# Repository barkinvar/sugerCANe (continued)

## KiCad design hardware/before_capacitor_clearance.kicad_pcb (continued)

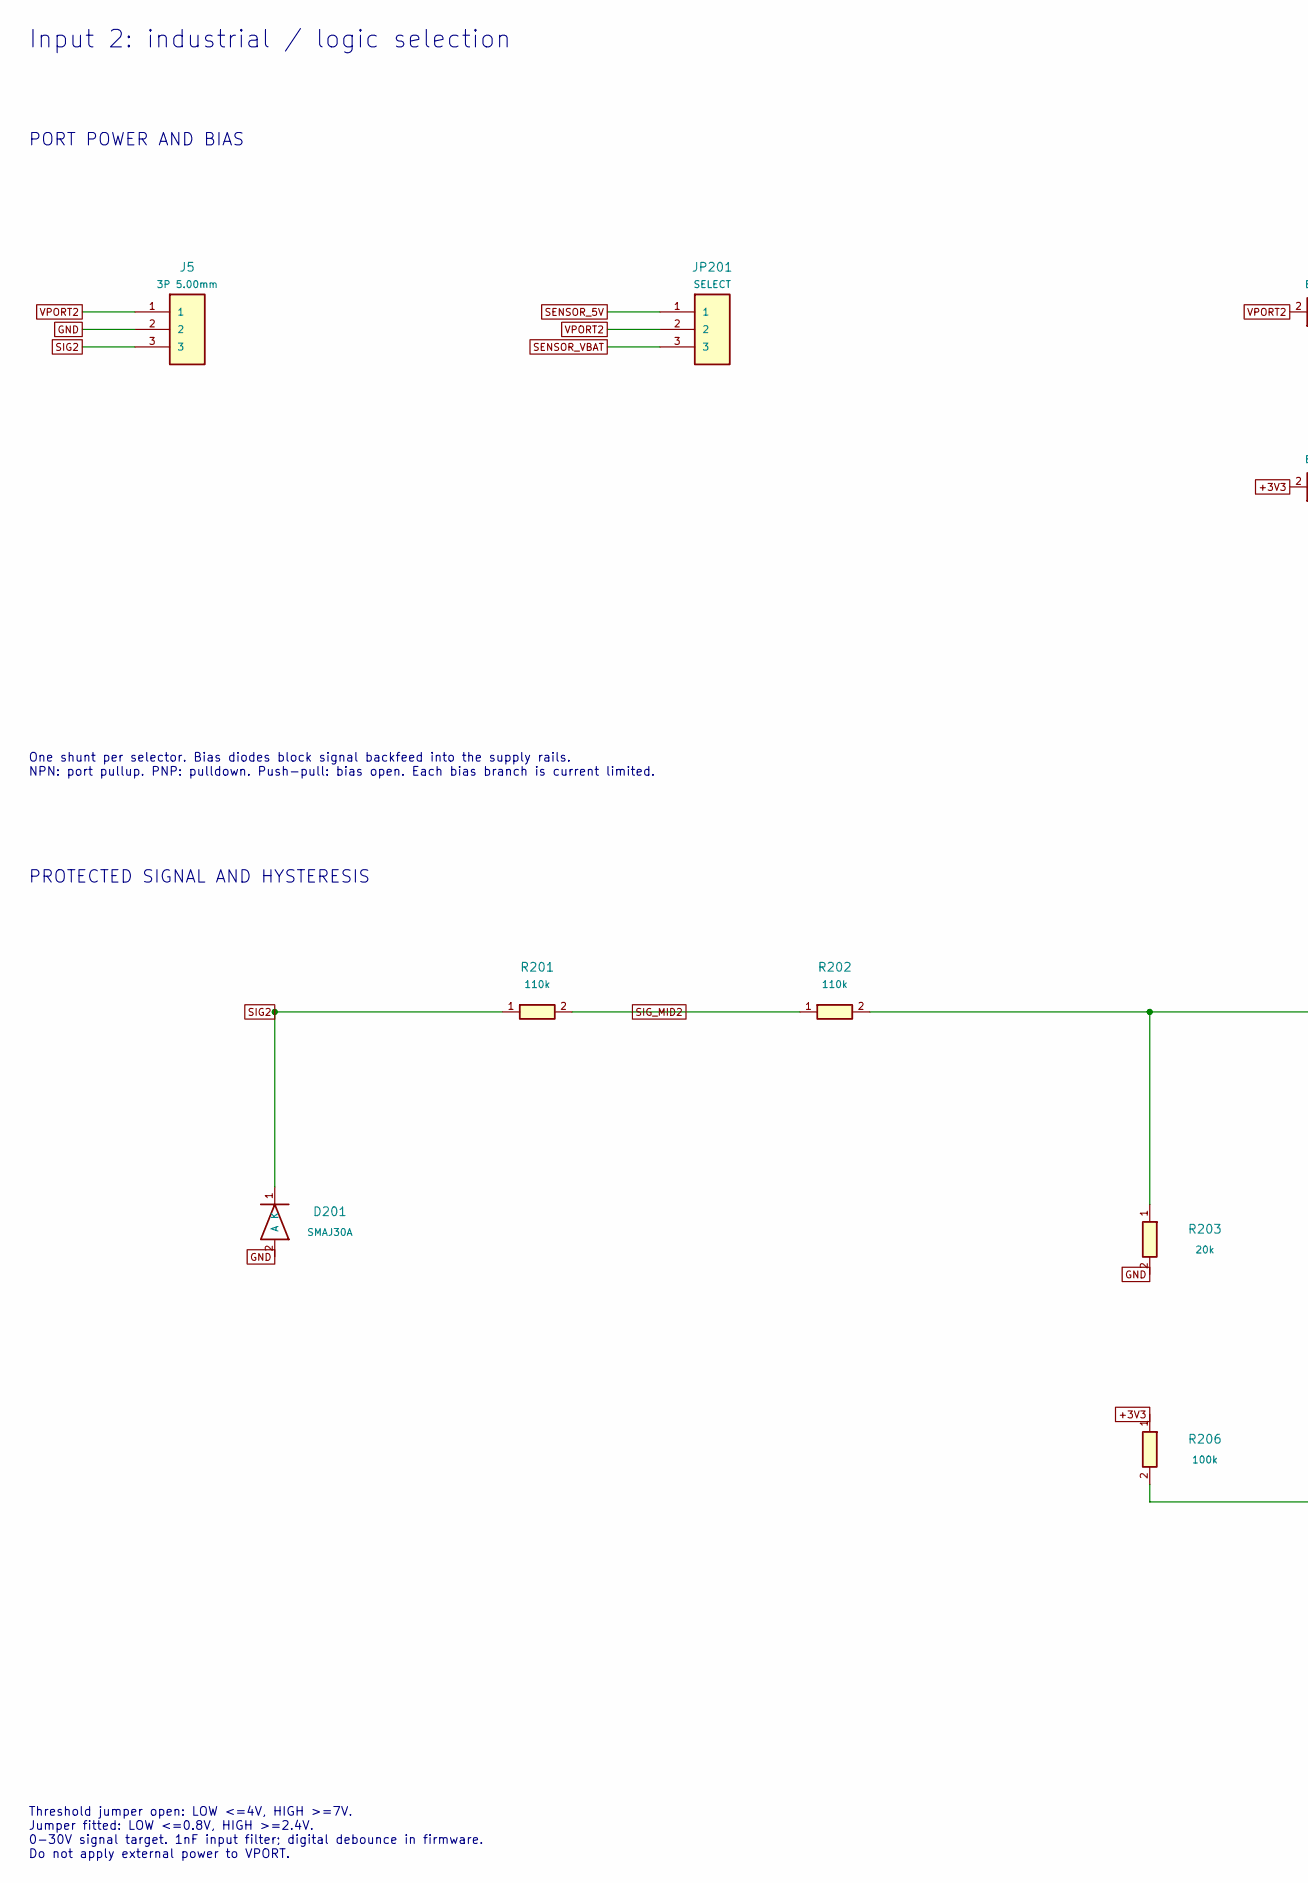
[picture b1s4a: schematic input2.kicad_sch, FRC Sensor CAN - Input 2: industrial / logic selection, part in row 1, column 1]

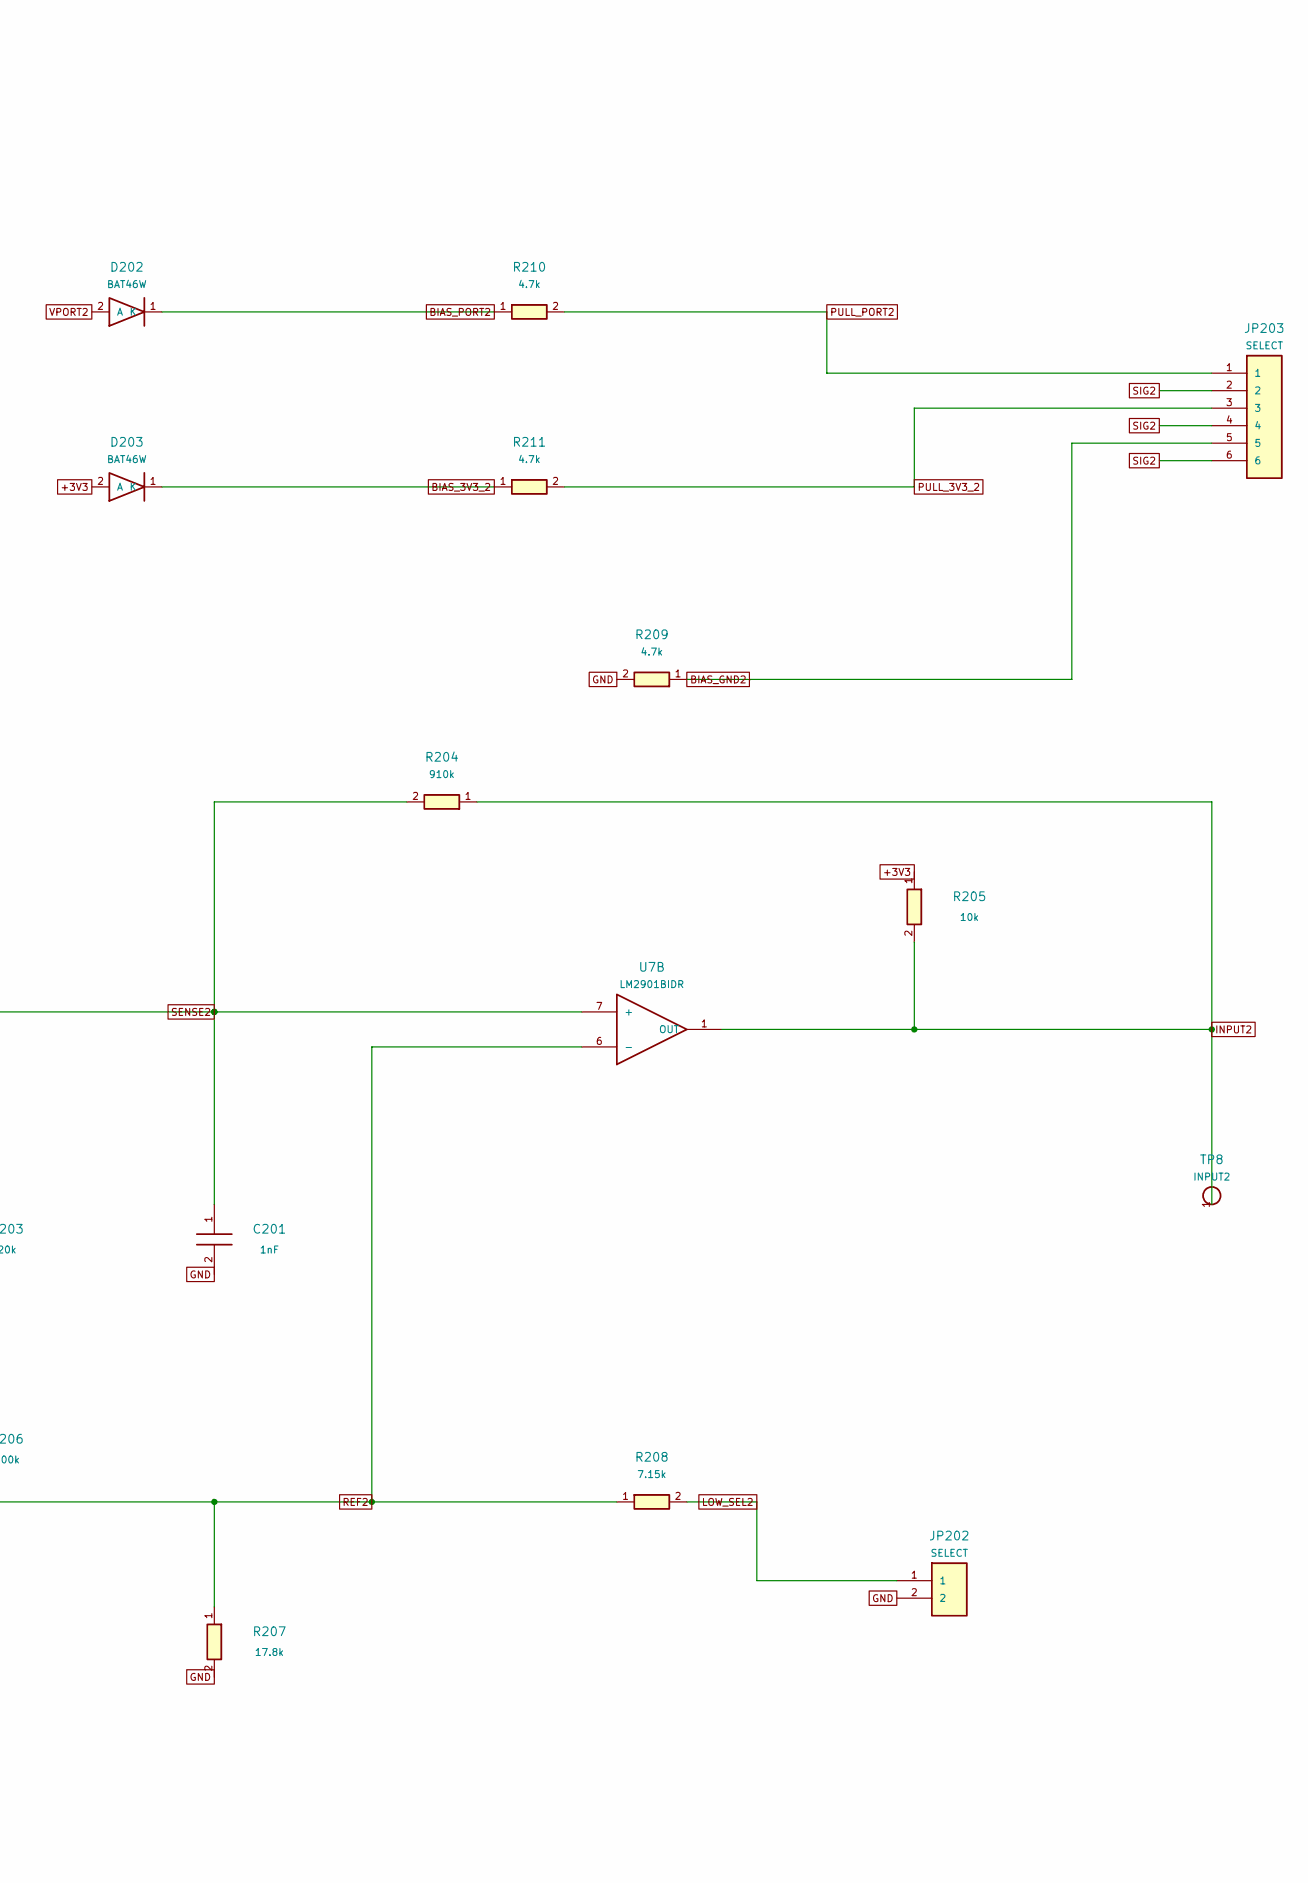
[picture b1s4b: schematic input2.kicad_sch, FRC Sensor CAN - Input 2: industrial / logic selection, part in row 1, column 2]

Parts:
C201: 1nF; C_0805_2012Metric; MPN CC0805JRNPO9BN102
D201: SMAJ30A; D_SMA; MPN SMAJ30A
D202, D203: BAT46W; D_SOD-123; MPN BAT46W-E3-18
J5: 3P 5.00mm; Wuerth_691137710003; MPN 691137710003
JP201: SELECT; PinHeader_1x03_P2.54mm_Vertical; MPN M20-9990345
JP202: SELECT; PinHeader_1x02_P2.54mm_Vertical; MPN M20-9990245
JP203: SELECT; PinHeader_2x03_P2.54mm_Vertical; MPN M20-9980345
R201, R202: 110k; R_0805_2012Metric; MPN RC0805FR-07110KL
R203: 20k; R_0805_2012Metric; MPN RC0805FR-0720KL
R204: 910k; R_0805_2012Metric; MPN RC0805FR-07910KL
R205: 10k; R_0805_2012Metric; MPN RC0805FR-0710KL
R206: 100k; R_0805_2012Metric; MPN RC0805FR-07100KL
R207: 17.8k; R_0805_2012Metric; MPN ERJ-6ENF1782V
R208: 7.15k; R_0805_2012Metric; MPN RC0805FR-077K15L
R209: 4.7k; R_2010_5025Metric; MPN RC2010FK-074K7L
R210, R211: 4.7k; R_0805_2012Metric; MPN RC0805FR-074K7L
TP8: INPUT2; TestPoint_Pad_D2.0mm
U7: LM2901BIDR; SOIC-14_3.9x8.7mm_P1.27mm; MPN LM2901BIDR

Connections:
+3V3: D203.2 (A), R205.1, R206.1; also elsewhere on the board
BIAS_3V3_2: D203.1 (K), R211.1
BIAS_GND2: JP203.5, R209.1
BIAS_PORT2: D202.1 (K), R210.1
GND: C201.2, D201.2 (A), J5.2, JP202.2, R203.2, R207.2, R209.2; also elsewhere on the board
INPUT2: R204.1, R205.2, TP8.1, U7.1 (OUT); also elsewhere on the board
LOW_SEL2: JP202.1, R208.2
PULL_3V3_2: JP203.3, R211.2
PULL_PORT2: JP203.1, R210.2
REF2: R206.2, R207.1, R208.1, U7.6 (-)
SENSE2: C201.1, R202.2, R203.1, R204.2, U7.7 (+)
SENSOR_5V: JP201.1; also elsewhere on the board
SENSOR_VBAT: JP201.3; also elsewhere on the board
SIG2: D201.1 (K), J5.3, JP203.2, JP203.4, JP203.6, R201.1
SIG_MID2: R201.2, R202.1
VPORT2: D202.2 (A), J5.1, JP201.2

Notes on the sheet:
Input 2: industrial / logic selection
PORT POWER AND BIAS
One shunt per selector. Bias diodes block signal backfeed into the supply rails. NPN: port pullup. PNP: pulldown. Push-pull: bias open. Each bias branch is current limited.
PROTECTED SIGNAL AND HYSTERESIS
Threshold jumper open: LOW <=4V, HIGH >=7V. Jumper fitted: LOW <=0.8V, HIGH >=2.4V. 0-30V signal target. 1nF input filter; digital debounce in firmware. Do not apply external power to VPORT.

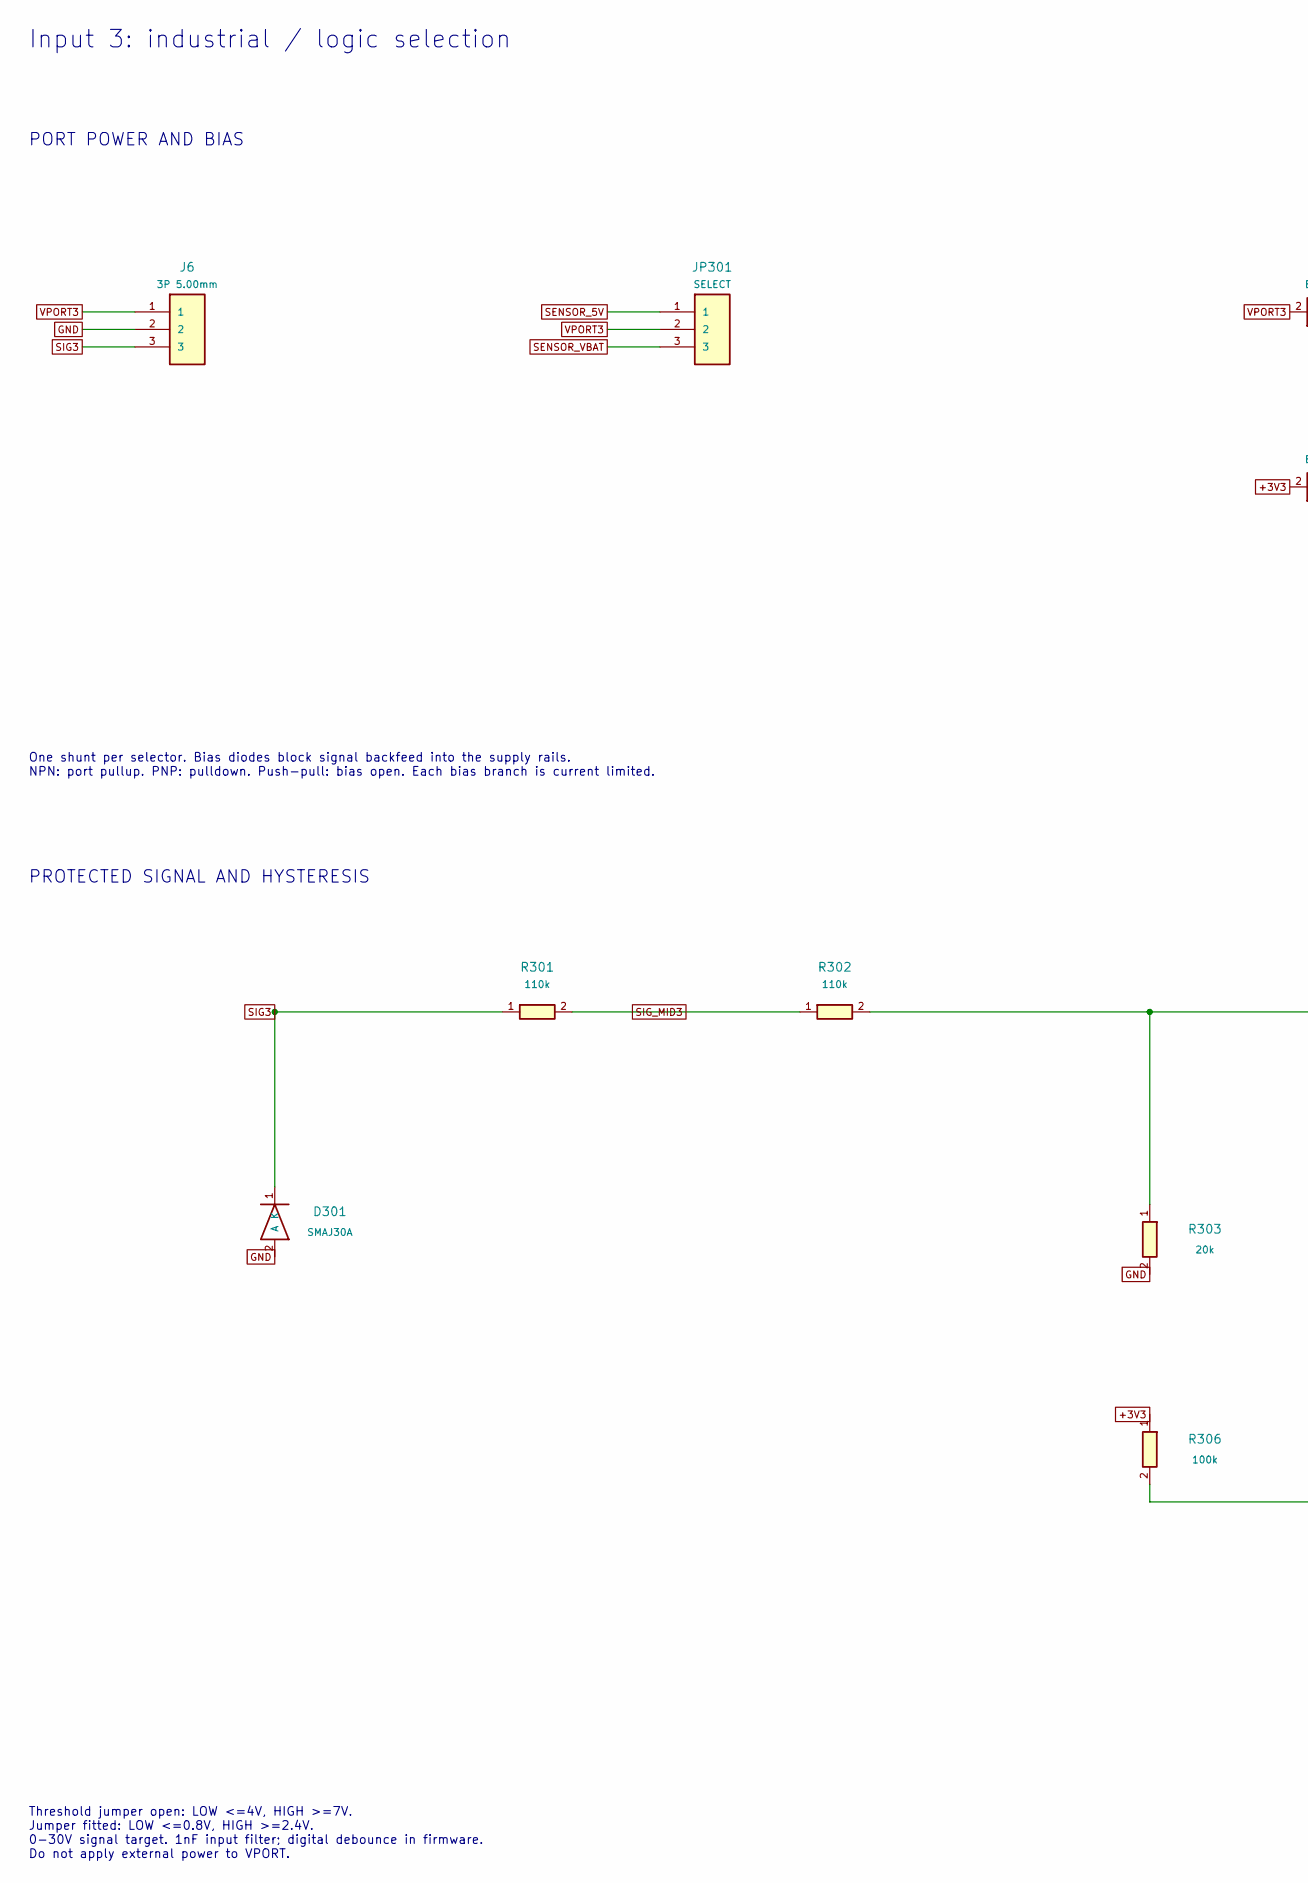
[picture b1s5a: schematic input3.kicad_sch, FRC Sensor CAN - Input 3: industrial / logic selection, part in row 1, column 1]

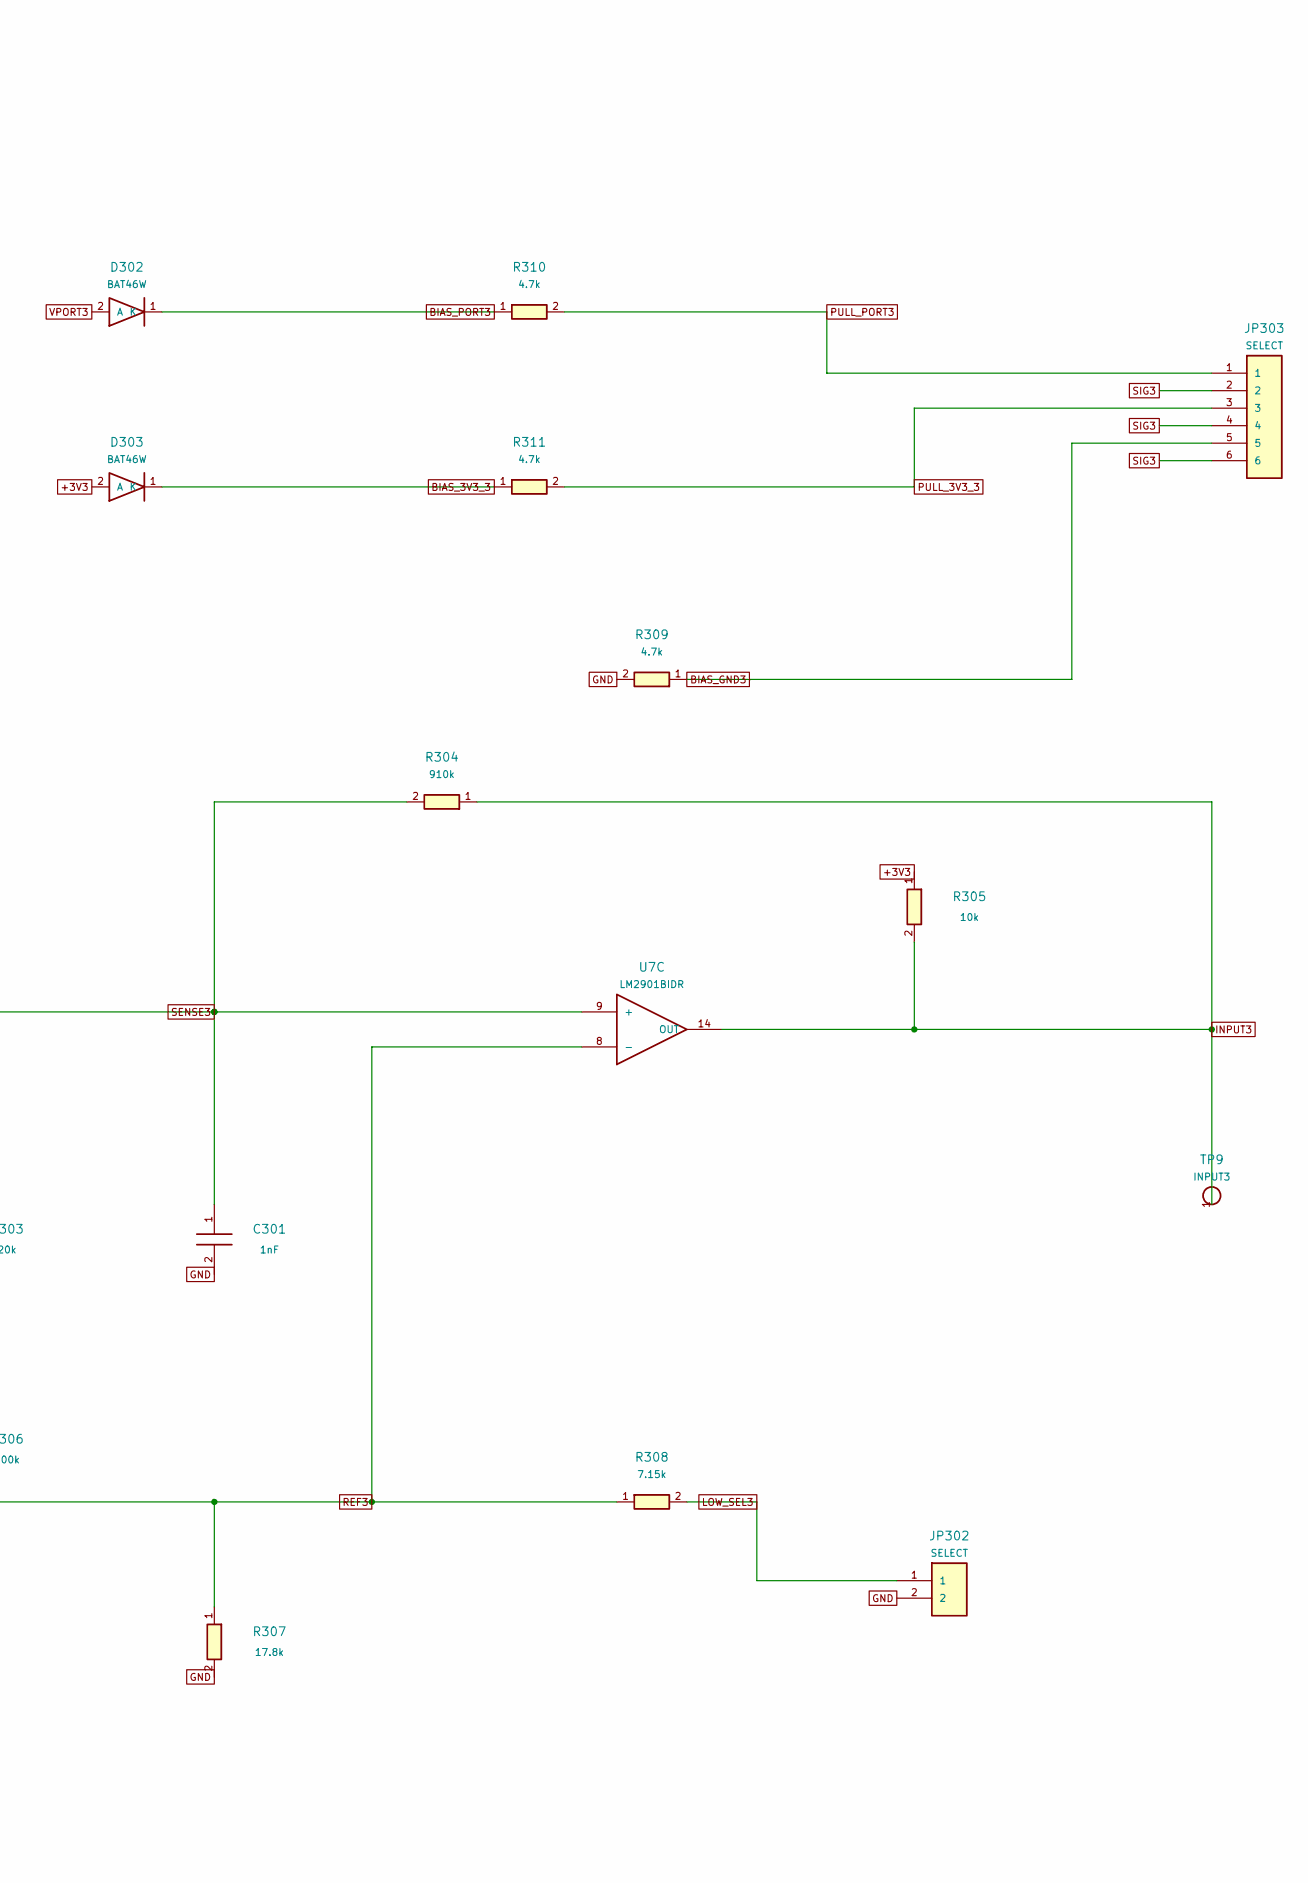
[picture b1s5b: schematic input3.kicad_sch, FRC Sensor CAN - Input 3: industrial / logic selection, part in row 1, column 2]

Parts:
C301: 1nF; C_0805_2012Metric; MPN CC0805JRNPO9BN102
D301: SMAJ30A; D_SMA; MPN SMAJ30A
D302, D303: BAT46W; D_SOD-123; MPN BAT46W-E3-18
J6: 3P 5.00mm; Wuerth_691137710003; MPN 691137710003
JP301: SELECT; PinHeader_1x03_P2.54mm_Vertical; MPN M20-9990345
JP302: SELECT; PinHeader_1x02_P2.54mm_Vertical; MPN M20-9990245
JP303: SELECT; PinHeader_2x03_P2.54mm_Vertical; MPN M20-9980345
R301, R302: 110k; R_0805_2012Metric; MPN RC0805FR-07110KL
R303: 20k; R_0805_2012Metric; MPN RC0805FR-0720KL
R304: 910k; R_0805_2012Metric; MPN RC0805FR-07910KL
R305: 10k; R_0805_2012Metric; MPN RC0805FR-0710KL
R306: 100k; R_0805_2012Metric; MPN RC0805FR-07100KL
R307: 17.8k; R_0805_2012Metric; MPN ERJ-6ENF1782V
R308: 7.15k; R_0805_2012Metric; MPN RC0805FR-077K15L
R309: 4.7k; R_2010_5025Metric; MPN RC2010FK-074K7L
R310, R311: 4.7k; R_0805_2012Metric; MPN RC0805FR-074K7L
TP9: INPUT3; TestPoint_Pad_D2.0mm
U7: LM2901BIDR; SOIC-14_3.9x8.7mm_P1.27mm; MPN LM2901BIDR

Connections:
+3V3: D303.2 (A), R305.1, R306.1; also elsewhere on the board
BIAS_3V3_3: D303.1 (K), R311.1
BIAS_GND3: JP303.5, R309.1
BIAS_PORT3: D302.1 (K), R310.1
GND: C301.2, D301.2 (A), J6.2, JP302.2, R303.2, R307.2, R309.2; also elsewhere on the board
INPUT3: R304.1, R305.2, TP9.1, U7.14 (OUT); also elsewhere on the board
LOW_SEL3: JP302.1, R308.2
PULL_3V3_3: JP303.3, R311.2
PULL_PORT3: JP303.1, R310.2
REF3: R306.2, R307.1, R308.1, U7.8 (-)
SENSE3: C301.1, R302.2, R303.1, R304.2, U7.9 (+)
SENSOR_5V: JP301.1; also elsewhere on the board
SENSOR_VBAT: JP301.3; also elsewhere on the board
SIG3: D301.1 (K), J6.3, JP303.2, JP303.4, JP303.6, R301.1
SIG_MID3: R301.2, R302.1
VPORT3: D302.2 (A), J6.1, JP301.2

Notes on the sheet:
Input 3: industrial / logic selection
PORT POWER AND BIAS
One shunt per selector. Bias diodes block signal backfeed into the supply rails. NPN: port pullup. PNP: pulldown. Push-pull: bias open. Each bias branch is current limited.
PROTECTED SIGNAL AND HYSTERESIS
Threshold jumper open: LOW <=4V, HIGH >=7V. Jumper fitted: LOW <=0.8V, HIGH >=2.4V. 0-30V signal target. 1nF input filter; digital debounce in firmware. Do not apply external power to VPORT.

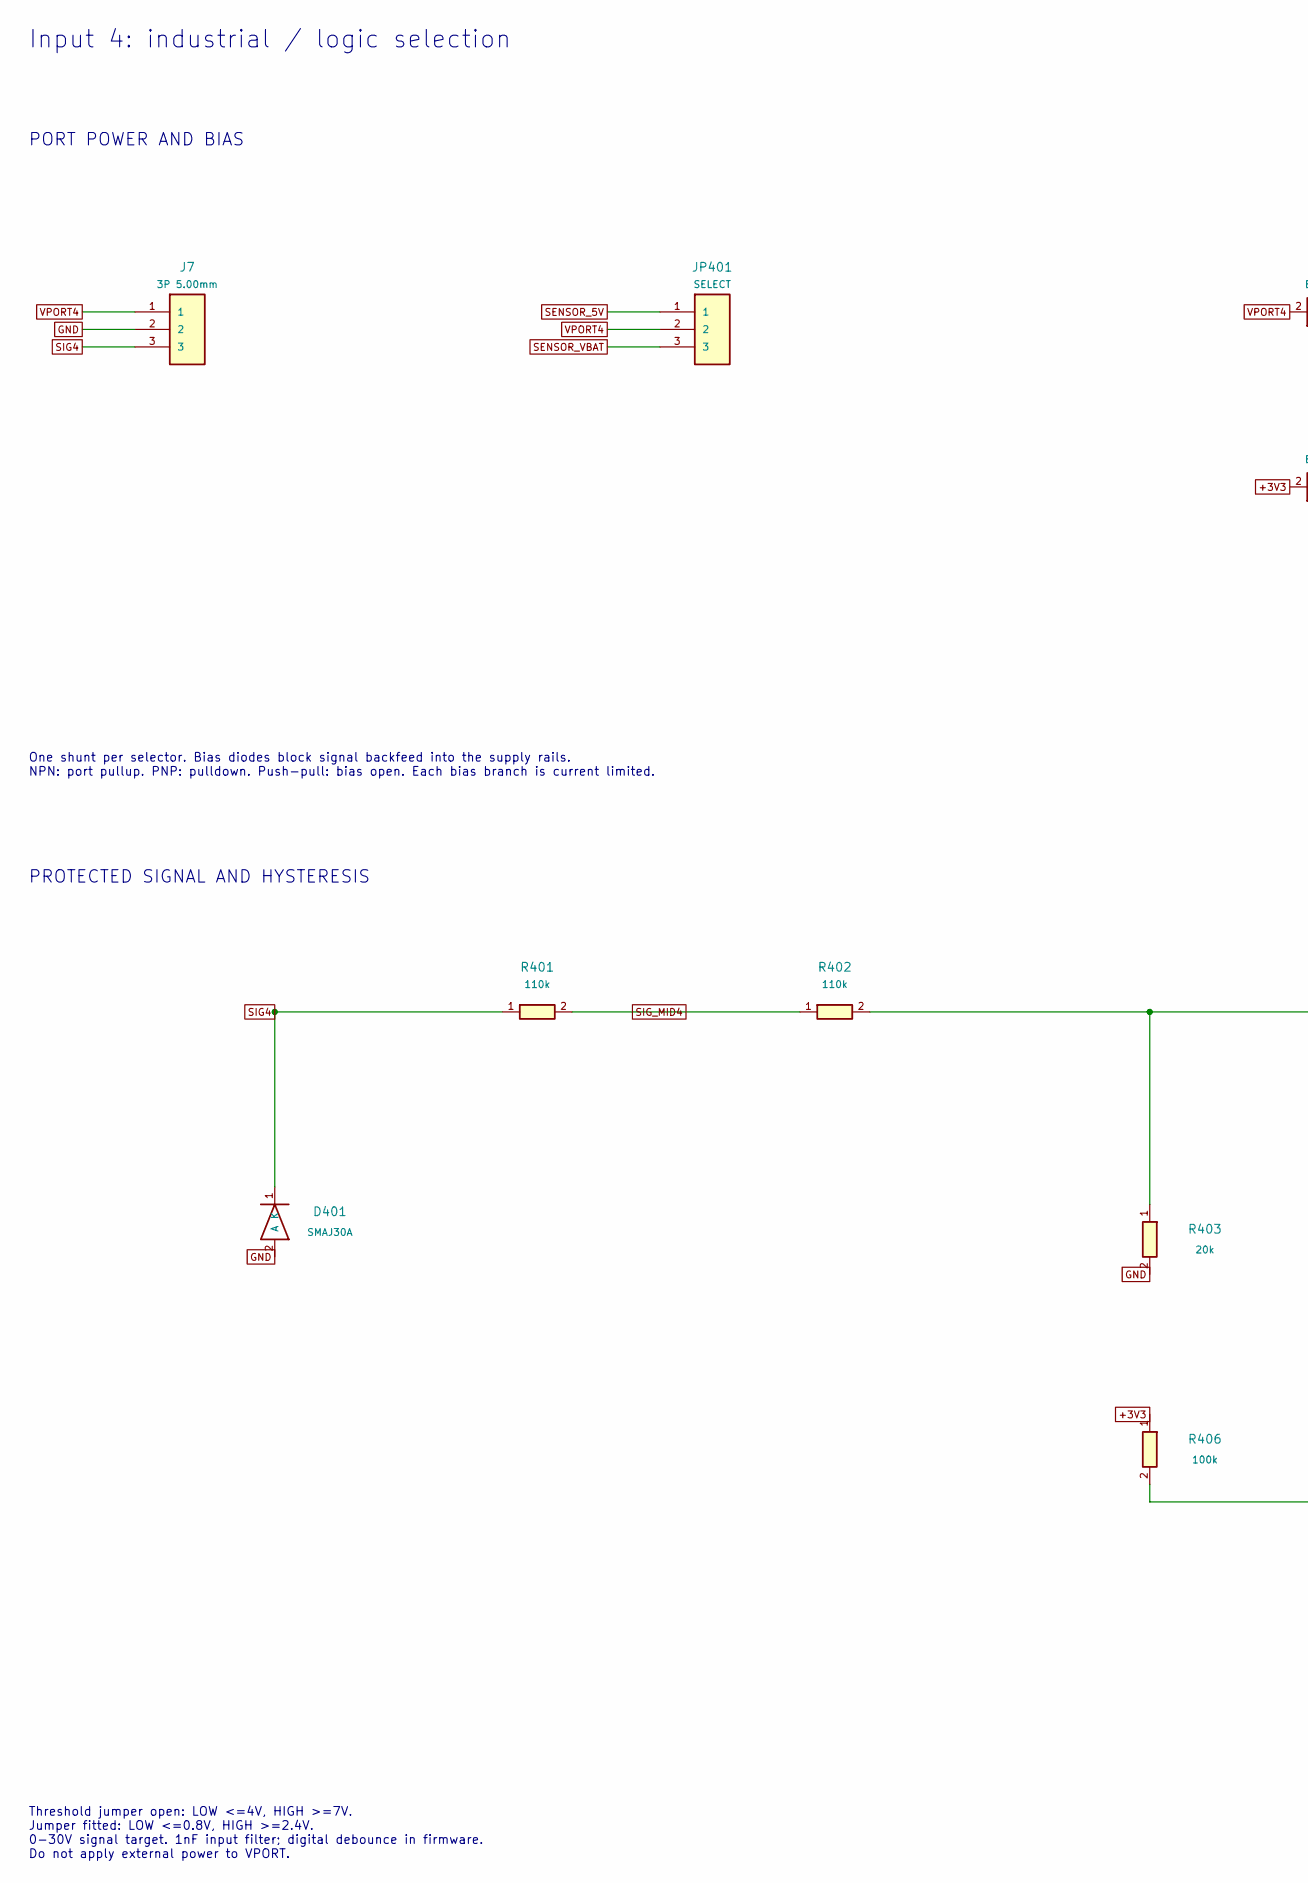
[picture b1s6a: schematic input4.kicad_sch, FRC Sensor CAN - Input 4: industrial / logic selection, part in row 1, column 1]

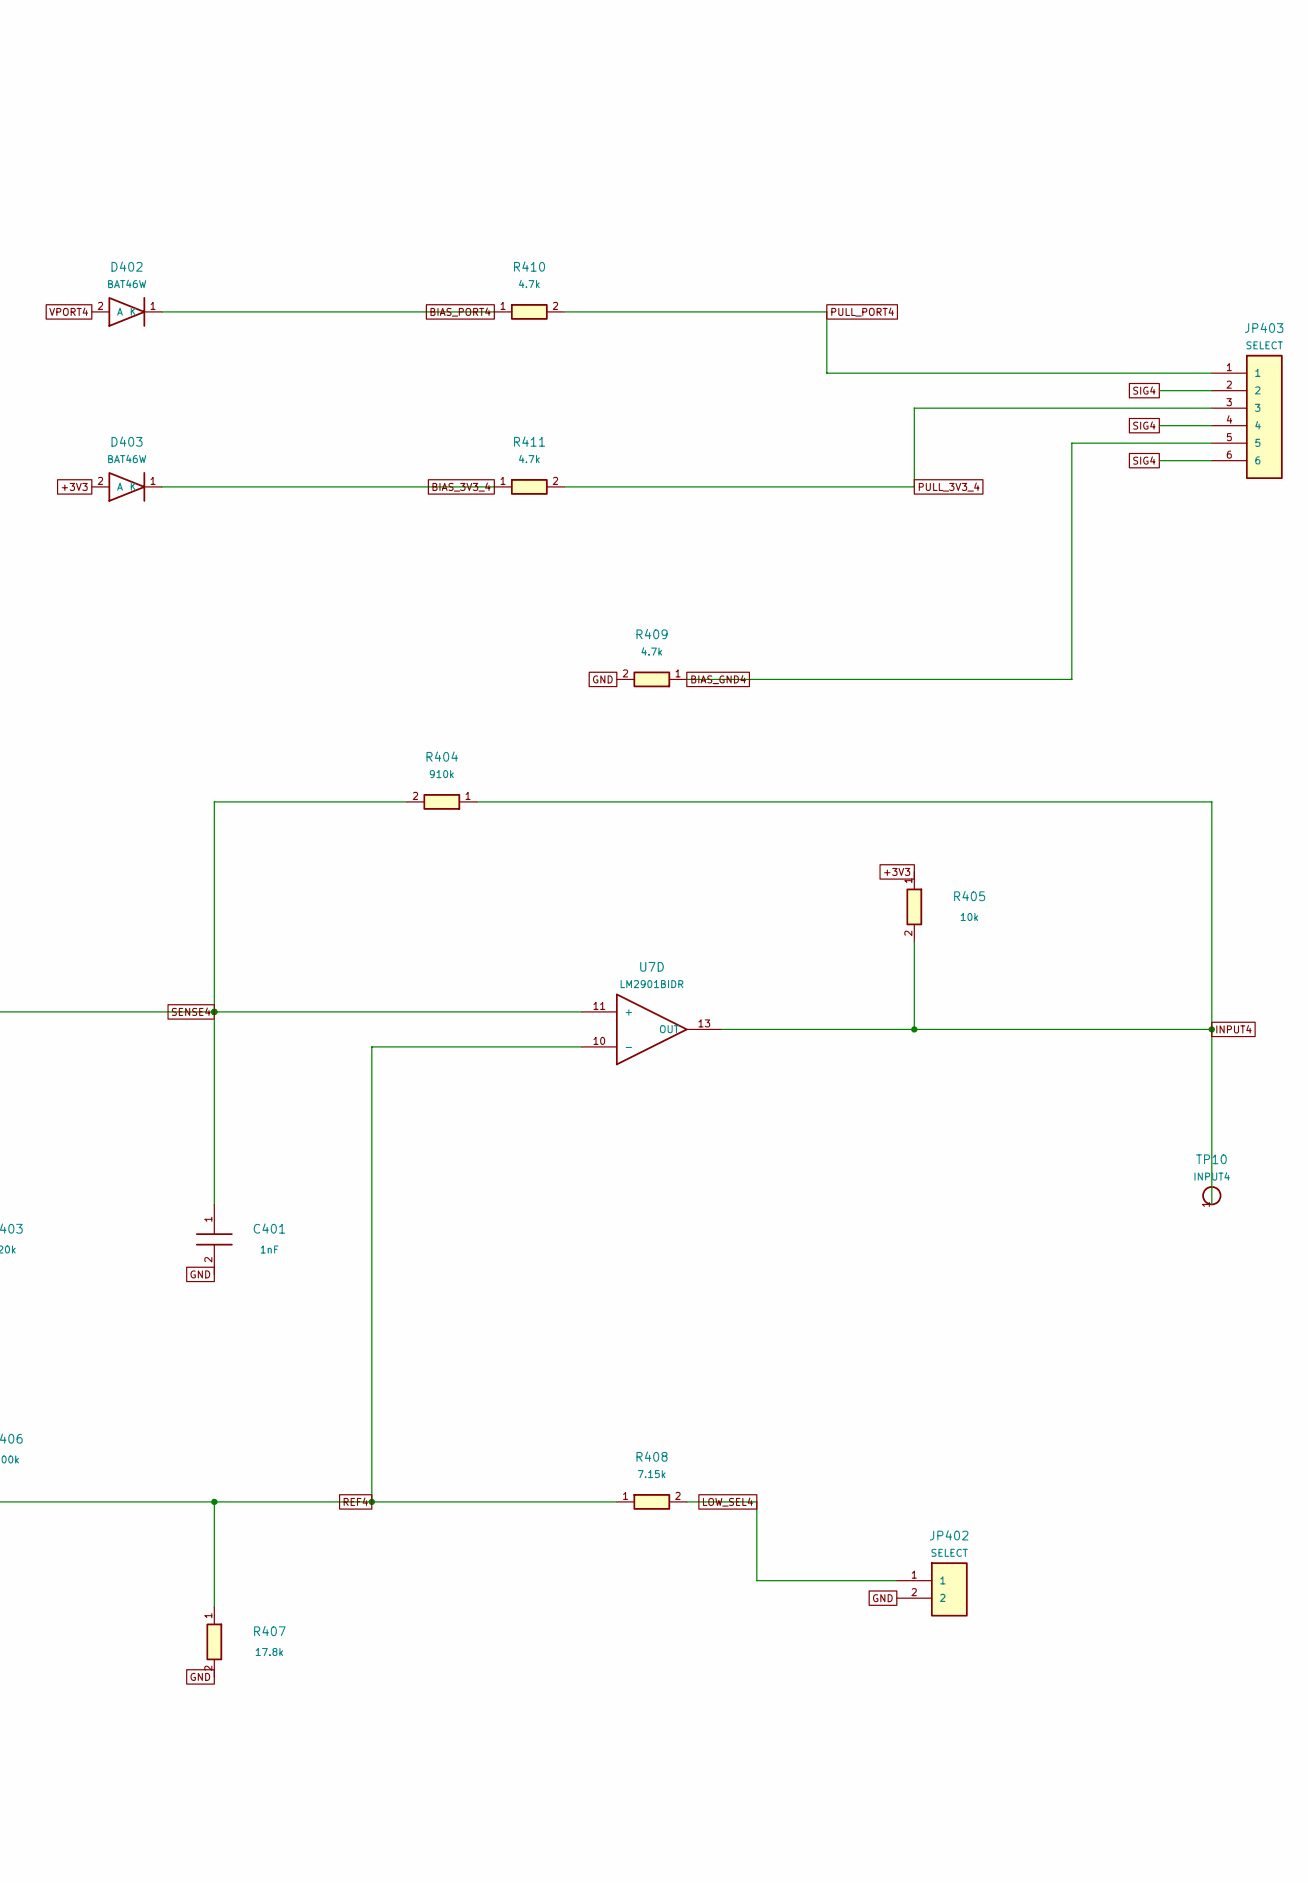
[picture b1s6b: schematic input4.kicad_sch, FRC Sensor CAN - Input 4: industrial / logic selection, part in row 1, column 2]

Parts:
C401: 1nF; C_0805_2012Metric; MPN CC0805JRNPO9BN102
D401: SMAJ30A; D_SMA; MPN SMAJ30A
D402, D403: BAT46W; D_SOD-123; MPN BAT46W-E3-18
J7: 3P 5.00mm; Wuerth_691137710003; MPN 691137710003
JP401: SELECT; PinHeader_1x03_P2.54mm_Vertical; MPN M20-9990345
JP402: SELECT; PinHeader_1x02_P2.54mm_Vertical; MPN M20-9990245
JP403: SELECT; PinHeader_2x03_P2.54mm_Vertical; MPN M20-9980345
R401, R402: 110k; R_0805_2012Metric; MPN RC0805FR-07110KL
R403: 20k; R_0805_2012Metric; MPN RC0805FR-0720KL
R404: 910k; R_0805_2012Metric; MPN RC0805FR-07910KL
R405: 10k; R_0805_2012Metric; MPN RC0805FR-0710KL
R406: 100k; R_0805_2012Metric; MPN RC0805FR-07100KL
R407: 17.8k; R_0805_2012Metric; MPN ERJ-6ENF1782V
R408: 7.15k; R_0805_2012Metric; MPN RC0805FR-077K15L
R409: 4.7k; R_2010_5025Metric; MPN RC2010FK-074K7L
R410, R411: 4.7k; R_0805_2012Metric; MPN RC0805FR-074K7L
TP10: INPUT4; TestPoint_Pad_D2.0mm
U7: LM2901BIDR; SOIC-14_3.9x8.7mm_P1.27mm; MPN LM2901BIDR

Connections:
+3V3: D403.2 (A), R405.1, R406.1; also elsewhere on the board
BIAS_3V3_4: D403.1 (K), R411.1
BIAS_GND4: JP403.5, R409.1
BIAS_PORT4: D402.1 (K), R410.1
GND: C401.2, D401.2 (A), J7.2, JP402.2, R403.2, R407.2, R409.2; also elsewhere on the board
INPUT4: R404.1, R405.2, TP10.1, U7.13 (OUT); also elsewhere on the board
LOW_SEL4: JP402.1, R408.2
PULL_3V3_4: JP403.3, R411.2
PULL_PORT4: JP403.1, R410.2
REF4: R406.2, R407.1, R408.1, U7.10 (-)
SENSE4: C401.1, R402.2, R403.1, R404.2, U7.11 (+)
SENSOR_5V: JP401.1; also elsewhere on the board
SENSOR_VBAT: JP401.3; also elsewhere on the board
SIG4: D401.1 (K), J7.3, JP403.2, JP403.4, JP403.6, R401.1
SIG_MID4: R401.2, R402.1
VPORT4: D402.2 (A), J7.1, JP401.2

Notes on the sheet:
Input 4: industrial / logic selection
PORT POWER AND BIAS
One shunt per selector. Bias diodes block signal backfeed into the supply rails. NPN: port pullup. PNP: pulldown. Push-pull: bias open. Each bias branch is current limited.
PROTECTED SIGNAL AND HYSTERESIS
Threshold jumper open: LOW <=4V, HIGH >=7V. Jumper fitted: LOW <=0.8V, HIGH >=2.4V. 0-30V signal target. 1nF input filter; digital debounce in firmware. Do not apply external power to VPORT.
